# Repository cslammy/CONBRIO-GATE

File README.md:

# CONBRIO-GATE
Synthesizer module that creates gates that speed up and slow down.
Please see the blog post here for more information:

https://audiodiwhy.blogspot.com/2021/12/con-brio-gate-boards-redesigned-to.html

This is a fix and redesign of the original project you can read about there.
https://audiodiwhy.blogspot.com/2019/04/conbrio-gate-generator-sounds-of-nature.html

Soundcloud demo for this module is here:
https://soundcloud.com/cslamm/con-brio-final

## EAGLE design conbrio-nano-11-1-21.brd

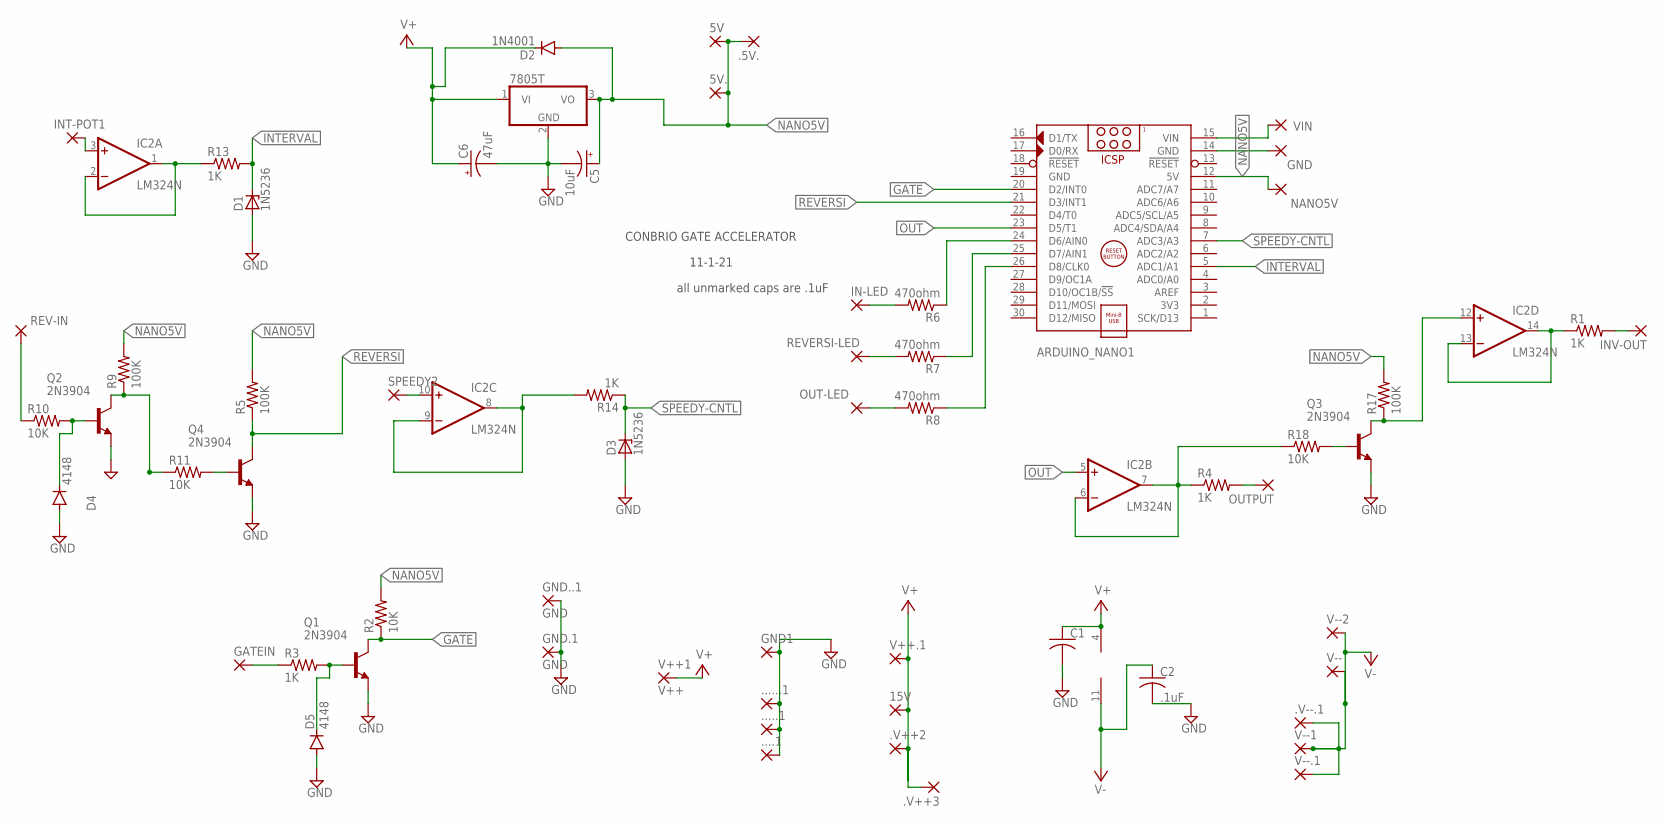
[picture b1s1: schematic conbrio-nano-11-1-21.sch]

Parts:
5V, .5V.: WIREPAD3,17/1,3; 3,17/1,3
5V.: WIREPAD3,17/1,2; 3,17/1,2
15V, .V++2, .V++3: 2,54/1,0
7805: 7805T; TO220H
....1, .....1, ......1, .V--.1: 3,17/1,3
ARDUINO_NANO1: ARDUINO_NANO
C1: C-US025-030X050; C025-030X050
C2: .1uF; C025-025X050
C5: 10uF; E3,5-10
C6: 47uF; E3,5-10
D1, D3: 1N5236; DO35Z10
D2: 1N4001; DO35-10
D4, D5: 4148; DO41-10
GATEIN: 3,17/1,3
GND, GND1: 3,17/1,3
GND.1, GND..1: GND; 1,6/0,8
IC2: LM324N; DIL14
IN-LED: 3,17/1,3
INT-POT1: 3,17/1,3
INV-OUT: 3,17/1,3
NANO5V: 3,17/1,3
OUT-LED: 3,17/1,3
OUTPUT: 3,17/1,3
Q1, Q2, Q3, Q4: 2N3904; TO92
R1: 1K; 0207/10
R2, R10, R11: 10K; 0204/7
R3, R13, R14: 1K; 0204/7
R4: 1K; 0207/12
R5, R9, R17: 100K; 0204/7
R6: 470ohm; 0207/10
R7, R8: 470ohm; 0204/7
R18: 10K; 0207/12
REV-IN: 3,17/1,3
REVERSI-LED: 3,17/1,3
SPEEDY2: 3,17/1,3
V++1: V++; 1,6/0,8
V++.1: 2,54/1,0
V--: WIREPAD3,17/1,1; 3,17/1,1
V--1, V--.1: 3,17/1,3
V--2: WIREPAD1,6/0,8; 1,6/0,8
VIN: 3,17/1,3

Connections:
GATE: ARDUINO_NANO1.20 (D2/INT0), Q1.1 (C), R2.1
GND: 7805.2 (GND), ....1.1, .....1.1, ......1.1, ARDUINO_NANO1.19 (GND), C1.2, C2.2, C5.-, C6.-, D1.A, D3.A, D4.A, D5.A, GND1.1, GND.1.1, GND..1.1, Q1.3 (E), Q2.3 (E), Q3.3 (E), Q4.3 (E)
INTERVAL: ARDUINO_NANO1.5 (ADC1/A1), D1.C, R13.2
INVOUT: IC2.13 (-IN), IC2.14 (OUT), R1.1
unnamed: GATEIN.1, R3.1
unnamed: D5.C, Q1.2 (B), R3.2
unnamed: INV-OUT.1, R1.2
unnamed: Q2.1 (C), R9.1, R11.1
unnamed: OUTPUT.1, R4.2
unnamed: IC2.3 (+IN), INT-POT1.1
unnamed: Q4.2 (B), R11.2
unnamed: IC2.6 (-IN), IC2.7 (OUT), R4.1, R18.1
unnamed: R10.1, REV-IN.1
unnamed: IN-LED.1, R6.2
unnamed: ARDUINO_NANO1.24 (D6/AIN0), R6.1
unnamed: R7.2, REVERSI-LED.1
unnamed: ARDUINO_NANO1.25 (D7/AIN1), R7.1
unnamed: OUT-LED.1, R8.2
unnamed: ARDUINO_NANO1.26 (D8/CLK0), R8.1
unnamed: IC2.12 (+IN), Q3.1 (C), R17.1
unnamed: IC2.10 (+IN), SPEEDY2.1
unnamed: D4.C, Q2.2 (B), R10.2
unnamed: IC2.1 (OUT), IC2.2 (-IN), R13.1
unnamed: Q3.2 (B), R18.2
unnamed: ARDUINO_NANO1.15 (VIN), VIN.1
unnamed: ARDUINO_NANO1.14 (GND), GND.1
NANO5V: 5V.1, 5V..1, 7805.3 (VO), .5V..1, ARDUINO_NANO1.12 (5V), C5.+, D2.A, NANO5V.1, R2.2, R5.2, R9.2, R17.2
OUT: ARDUINO_NANO1.23 (D5/T1), IC2.5 (+IN)
REVERSI: ARDUINO_NANO1.21 (D3/INT1), Q4.1 (C), R5.1
SPEEDY: IC2.8 (OUT), IC2.9 (-IN), R14.2
SPEEDY-CNTL: ARDUINO_NANO1.7 (ADC3/A3), D3.C, R14.1
V+: 15V.1, 7805.1 (VI), .V++2.1, .V++3.1, C1.1, C6.+, D2.C, IC2.4 (V+), V++1.1, V++.1.1
V-: .V--.1.1, C2.1, IC2.11 (V-), V--.1, V--1.1, V--2.1, V--.1.1

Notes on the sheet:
CONBRIO GATE ACCELERATOR
11-1-21
all unmarked caps are .1uF

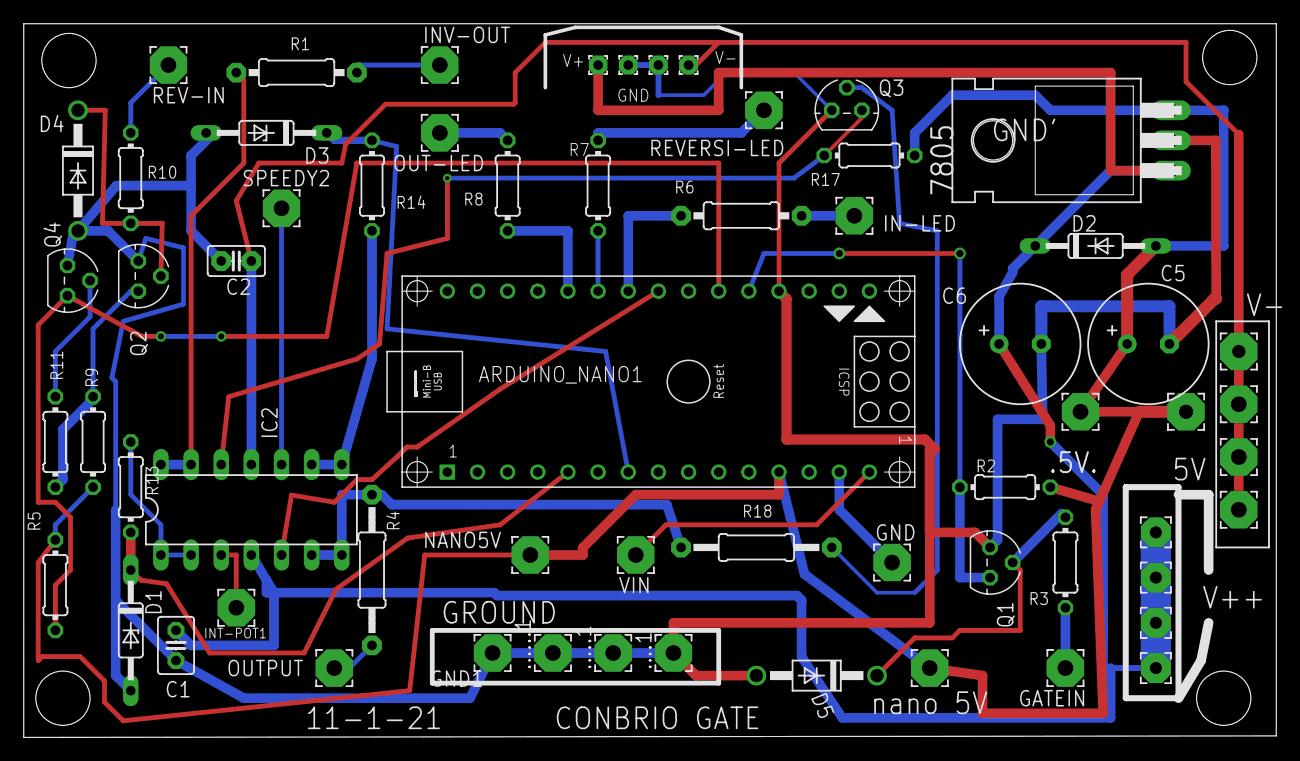
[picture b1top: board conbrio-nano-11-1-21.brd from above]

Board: 2 copper layers, 105.5 x 60.1 mm, 62 parts (0 on the bottom side), 33 nets.

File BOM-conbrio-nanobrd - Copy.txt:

7805          7805T  7805T              TO220H       Positive VOLTAGE REGULATOR                                 
ARDUINO_NANO1        ARDUINO_NANO       ARDUINO_NANO Arduino Nano V3.0 Module                                   
C1            .1uF   C-US025-030X050    C025-030X050 CAPACITOR, American symbol                                 
C2            .1uF   C-US025-025X050    C025-025X050 CAPACITOR, American symbol                                 
C5            10uF   CPOL-USE3.5-10     E3,5-10      POLARIZED CAPACITOR, American symbol            C          
C6            47uF   CPOL-USE3.5-10     E3,5-10      POLARIZED CAPACITOR, American symbol            C          
D1            1N5236 ZENER-DIODEDO35Z10 DO35Z10      Z-Diode 5V                                                   
D2            1N4001 1N4148DO35-10      DO35-10      DIODE                                21                    
D3            1N5236 ZENER-DIODEDO35Z10 DO35Z10      Z-Diode 5V                                                   
D4            4148   1N4004             DO41-10      DIODE                                82                    
D5            4148   1N4004             DO41-10      DIODE                                82                    
               
IC2           LM324N LM324N             DIL14        OP AMP   

Note, for IC2, please do not use jfet opamp like TL084. LM324 or LM358 DIP IC is more reliable for this design.
                     
Q1            2N3904 2N3904             TO92         NPN Transistor                                             
Q2            2N3904 2N3904             TO92         NPN Transistor                                             
Q3            2N3904 2N3904             TO92         NPN Transistor                                             
Q4            2N3904 2N3904             TO92         NPN Transistor                                             
R1            1K     R-US_0207/10       0207/10      RESISTOR, American symbol                                  
R2            10K    R-US_0204/7        0204/7       RESISTOR, American symbol                                  
R3            1K     R-US_0204/7        0204/7       RESISTOR, American symbol                                  
R4            1K     R-US_0207/12       0207/12      RESISTOR, American symbol                                  
R5            100K   R-US_0204/7        0204/7       RESISTOR, American symbol                                  
R6            470ohm R-US_0207/10       0207/10      RESISTOR, American symbol                                  
R7            470ohm R-US_0204/7        0204/7       RESISTOR, American symbol                                  
R8            470ohm R-US_0204/7        0204/7       RESISTOR, American symbol                                  
R9            100K   R-US_0204/7        0204/7       RESISTOR, American symbol                                  
R10           10K    R-US_0204/7        0204/7       RESISTOR, American symbol                                  
R11           10K    R-US_0204/7        0204/7       RESISTOR, American symbol                                  
R13           1K     R-US_0204/7        0204/7       RESISTOR, American symbol                                  
R14           1K     R-US_0204/7        0204/7       RESISTOR, American symbol                                  
R17           100K   R-US_0204/7        0204/7       RESISTOR, American symbol                                  
R18           10K    R-US_0207/12       0207/12      RESISTOR, American symbol

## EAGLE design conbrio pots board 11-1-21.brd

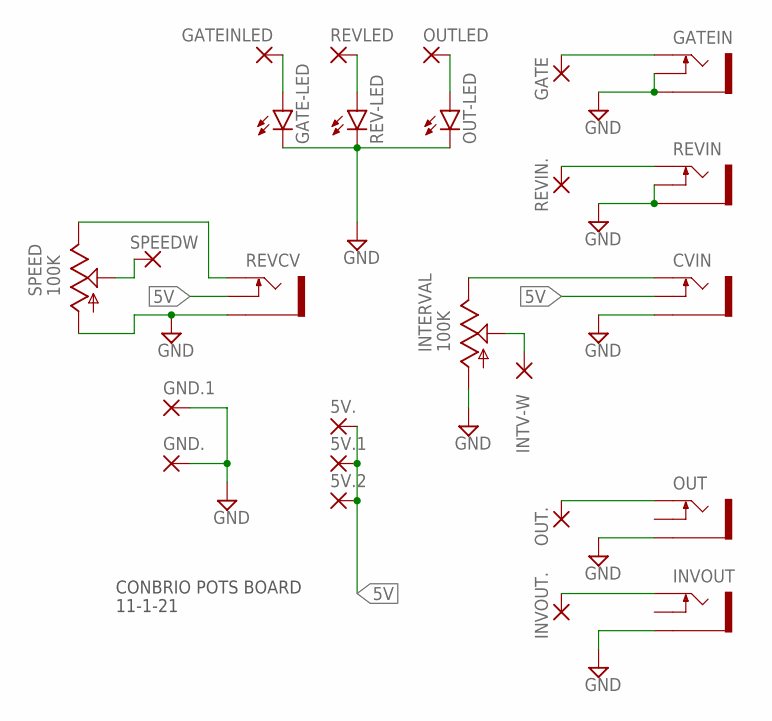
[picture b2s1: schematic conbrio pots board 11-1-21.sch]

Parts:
5V., 5V.1, 5V.2: WIREPAD3,17/1,3; 3,17/1,3
CVIN: THONKICONNNEW; WQP-PJ301M-12_JACK
GATE: WIREPAD3,17/1,3; 3,17/1,3
GATE-LED: LED3MM
GATEIN: THONKICONNNEW; WQP-PJ301M-12_JACK
GATEINLED: WIREPAD3,17/1,3; 3,17/1,3
GND., GND.1: WIREPAD3,17/1,3; 3,17/1,3
INTERVAL: 100K; 9MM_SNAP-IN_POT
INTV-W: WIREPAD3,17/1,3; 3,17/1,3
INVOUT: THONKICONNNEW; WQP-PJ301M-12_JACK
INVOUT.: WIREPAD3,17/1,3; 3,17/1,3
OUT: THONKICONNNEW; WQP-PJ301M-12_JACK
OUT-LED: LED3MM
OUT.: WIREPAD3,17/1,3; 3,17/1,3
OUTLED: WIREPAD3,17/1,3; 3,17/1,3
REV-LED: LED3MM
REVCV: THONKICONNNEW; WQP-PJ301M-12_JACK
REVIN: THONKICONNNEW; WQP-PJ301M-12_JACK
REVIN.: WIREPAD3,17/1,3; 3,17/1,3
REVLED: WIREPAD3,17/1,3; 3,17/1,3
SPEED: 100K; 9MM_SNAP-IN_POT
SPEEDW: WIREPAD3,17/1,3; 3,17/1,3

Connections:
5V: 5V..1, 5V.1.1, 5V.2.1, CVIN.P$2_SWITCH (SWITCH), REVCV.P$2_SWITCH (SWITCH)
GND: CVIN.P$3_SLEEVE (SLEEVE), GATE-LED.K (C), GATEIN.P$2_SWITCH (SWITCH), GATEIN.P$3_SLEEVE (SLEEVE), GND..1, GND.1.1, INTERVAL.1 (A), INVOUT.P$3_SLEEVE (SLEEVE), OUT.P$3_SLEEVE (SLEEVE), OUT-LED.K (C), REV-LED.K (C), REVCV.P$3_SLEEVE (SLEEVE), REVIN.P$2_SWITCH (SWITCH), REVIN.P$3_SLEEVE (SLEEVE), SPEED.1 (A)
unnamed: GATE-LED.A, GATEINLED.1
unnamed: REV-LED.A, REVLED.1
unnamed: OUT-LED.A, OUTLED.1
unnamed: CVIN.P$1_TIP (TIP), INTERVAL.3 (E)
unnamed: INTERVAL.2 (S), INTV-W.1
unnamed: REVCV.P$1_TIP (TIP), SPEED.3 (E)
unnamed: SPEED.2 (S), SPEEDW.1
unnamed: GATE.1, GATEIN.P$1_TIP (TIP)
unnamed: REVIN.P$1_TIP (TIP), REVIN..1
unnamed: OUT.P$1_TIP (TIP), OUT..1
unnamed: INVOUT.P$1_TIP (TIP), INVOUT..1

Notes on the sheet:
CONBRIO POTS BOARD
11-1-21

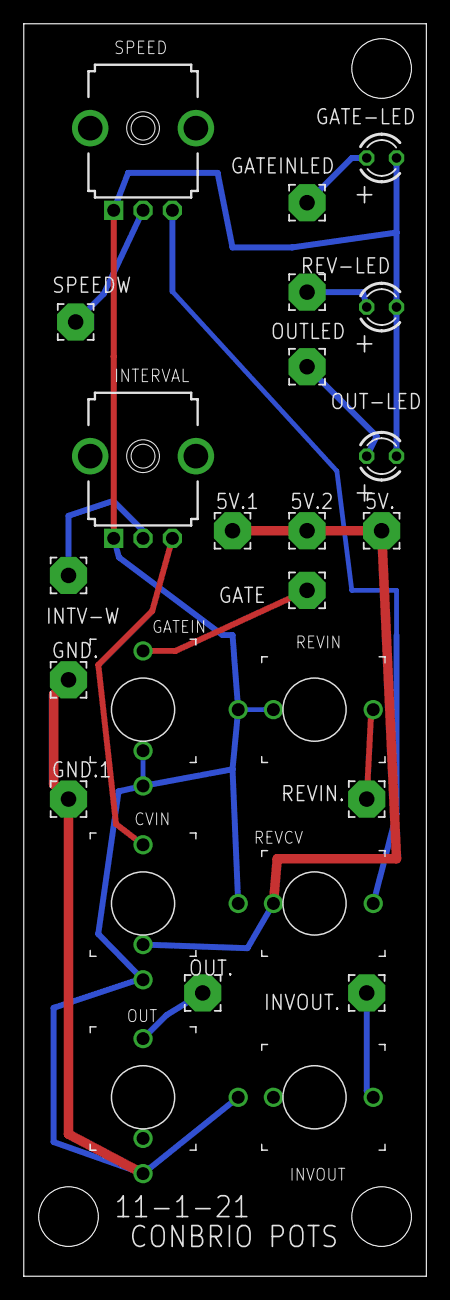
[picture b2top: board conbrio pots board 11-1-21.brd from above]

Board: 2 copper layers, 34.3 x 106.7 mm, 25 parts (0 on the bottom side), 13 nets.

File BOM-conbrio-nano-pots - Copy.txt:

BOM-conbrio-nano-pots  for 11-1-21 design       

CVIN      THONKICONNNEW THONKICONNNEW    WQP-PJ301M-12_JACK 3.5mm socket for Eurorack modular synths                    
INVOUT    THONKICONNNEW THONKICONNNEW    WQP-PJ301M-12_JACK 3.5mm socket for Eurorack modular synths                    
OUT       THONKICONNNEW THONKICONNNEW    WQP-PJ301M-12_JACK 3.5mm socket for Eurorack modular synths 
GATEIN    THONKICONNNEW THONKICONNNEW    WQP-PJ301M-12_JACK 3.5mm socket for Eurorack modular synths      
REVCV     THONKICONNNEW THONKICONNNEW    WQP-PJ301M-12_JACK 3.5mm socket for Eurorack modular synths                    
REVIN     THONKICONNNEW THONKICONNNEW    WQP-PJ301M-12_JACK 3.5mm socket for Eurorack modular synths   
GATE-LED                LED3MM           LED3MM             LED                                               97        
OUT-LED                 LED3MM           LED3MM             LED                                               97        
REV-LED                 LED3MM           LED3MM             LED                                               97                
SPEED     100K          9MM_SNAP-IN_POT_ 9MM_SNAP-IN_POT    9mm vertical snap-in pot, Alpha / Panasonic style      
INTERVAL  100K          9MM_SNAP-IN_POT_ 9MM_SNAP-IN_POT    9mm vertical snap-in pot, Alpha / Panasonic style

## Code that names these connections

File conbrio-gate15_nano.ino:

//loaded 11-12-18 6:12PM

//attiny interrupt test
//https://thewanderingengineer.com/2014/08/11/pin-change-interrupts-on-attiny85/

//version 3 basic idea
//version 4 fixed interrupt so it works like a gate
//version 5 get random shit going
//version 6 control interval w' pot
//version 7 cleaned up interrupt gate and general fixes.
//version 8 got most of Attiny going but ran out of pins
//version 9 ported to nano (more pins!)
//version 13 got rid of interrupts, changed gate logic, tweaked pot values.
//version 14 added LED I/O, set delays
//version 15 switched reversi logic (buffer no longer inverts--new hardware)

#define F_CPU 1000000UL
#include <avr/io.h>
#include <util/delay.h>
#include <avr/interrupt.h>



const byte blink=13; // built in LED port on nano
boolean gateon = LOW; // logic used for gated elements LOW or HIGH
int x = 0;
int a = 0;
int b = 0;
int c = 0;
int d = 0;
int e = 0;

float upwards = 0;
long randomnumber = 0;
//int printme = 0;
int headsortails = 0;
int interval = 0;  //how long for initial interval read
int interval2 = 0; // use this to control blinking
int speedy = 0; // length between blinks
boolean reverski=HIGH; // do we go fast to slow or slow to fast?
int randomvalue = 15;  // add musicality to your dukey.
int xx = 1;
void setup()
{
    Serial.begin( 9600 );
   
// interrupt on for Nano
  


  pinMode(A1, INPUT); // interval 0 - 300
  pinMode(A3, INPUT); // speedy.  distance between each pulse.
  pinMode(3, INPUT); //reverski.  fast to slow or slow to fast
  pinMode(2, INPUT); // gate in used as INT0
  pinMode(8, OUTPUT); //LED for gate output 
  pinMode(6, OUTPUT); // LED for gate input
  pinMode(7, OUTPUT); // LED for reverski status
  pinMode(blink, OUTPUT); // internal LED on Nano

  
 // attachInterrupt(digitalPinToInterrupt(3), myisr2, HIGH); // reverski signal 
//  attachInterrupt(digitalPinToInterrupt(2), myisr, HIGH); // get gate signal; LOW is TRUE 
}


//"waitaround" lets you avoid delay() stupidity.  220 is about 1 second on a 1Mhz ATTINY85
void waitaround (int x)
{
 for (a = 0;a < x;a++)
  waitaround3(x);
}

void waitaround2 (int x)


{
 for (b = 0;b < x;b++)
 x = x;
}

void waitaround3 (int x)
{
  for (c = 0;c < x;c++)
  waitaround2(x);
}





void loop()

{
delay(10);
reverski = digitalRead(3);
gateon = digitalRead(2);
//Serial.println(reverski);  

//this is getslower routine.

if (reverski == LOW)
    {
      
    digitalWrite(7,LOW); // turn LED **OFF** which means we are in get slower mode
    
    if (xx == 0)
    {
    interval = (analogRead(A1));
    xx = 1;
    }
    //Serial.println("reverski is:");
    //Serial.println(reverski);
       if (gateon==LOW)
       {
         digitalWrite(6,HIGH); // turn on gate in status LED
   //    Serial.println("gateon in getslowweris:");

     //  Serial.println("gateon upwards = interval; is true in getslower loop");
 
   

 /*      Serial.print("interval:");      
       Serial.println(interval);
       Serial.print("speedy is:");
       Serial.println(speedy);

  */      
   
 
        
        headsortails = random(1,2);
        
        randomnumber = random(randomvalue);   
       
         digitalWrite(blink,HIGH);
         digitalWrite(8,HIGH); // lite LED that gate out is on
         digitalWrite(5,HIGH); // Send 5V to output buffer
         
         waitaround(interval* .5);
         digitalWrite(blink,LOW);
         digitalWrite(8,LOW); // un-lite LED that gate out is on
         digitalWrite(5,LOW); // Send GND to output buffer     
                  
                  waitaround(interval* .5);


          speedy = (analogRead(A3)/5);
       
          if (headsortails == 1)
           {
           interval = interval + speedy + randomnumber; 
           }
          else
           {
           interval = interval + speedy;
           }


         } 
         if (gateon==HIGH)
         {
          digitalWrite(blink,LOW);
          digitalWrite(6, LOW); // turn off input status LED
          xx = 0;    
         }

      
   }  // end if reverski


//THIS IS THE GET FASTER ROUTINE.

if (reverski == HIGH)
    {
         digitalWrite(7, HIGH);  // turn reverski LED **ON** which means we are get faster mode.
         
         delay(10);
         if (xx == 1)
            {
              interval2 = (analogRead(A1));             
            }       
         if (gateon==LOW)
            { 
             digitalWrite(6,HIGH); // turn on gate input status LED 
            xx = 0; // don't get a new read for interval2   
 //         Serial.println("gateon is LOW in get faster loop");
         
            headsortails = random(1,2);
            randomnumber = random(randomvalue);   
            waitaround(interval2);   
            digitalWrite(blink,HIGH);
            digitalWrite(8,HIGH); // lite LED that gate out is on
            digitalWrite(5,HIGH); // Send 5V to output buffer
            
            waitaround(interval2);
            digitalWrite(blink,LOW);
                   
            digitalWrite(8,LOW); // un-lite LED that gate out is on
            digitalWrite(5,LOW); // Send gnd to output buffer
            speedy = (analogRead(A3)/20);

            

            
            if (headsortails == 1)
            
                            
                {
                interval2 = interval2 - (speedy-randomnumber);
                }

           
                              
              else
                {
                interval2 = interval2 - (speedy + randomnumber);
                }

               if (interval2 < 5)
               {
                interval2 = 70;
               }
        
              
        } // end while gateon == LOW
        if (gateon==HIGH)
        {
          digitalWrite(blink,LOW);
          digitalWrite(6,LOW); // turn off gate input status LED
          
          xx = 1;
          speedy = 0;
        } // end gateon = high
    } // END IF REVERSKI HIGH

} // end loop ()

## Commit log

2021-12-27 PDF of schems and boards for this module
2021-12-27 Initial upload
    Gerbers for pots and main "nano" board
2021-12-27 Initial Upload
    BOM for project
2021-12-27 Fixed comment typo
2021-12-27 Add files via upload
    Arduino sketch INO file for Arduino Nano for this project.
2021-12-27 Add files via upload
    Eagle SCH (schematic) and BRD (Board) files for this module
2021-12-27 Add files via upload
    PDF for schematics and Boards for this project.
2021-12-27 Add files via upload
    Wiring between POTS and NANO board for this project
